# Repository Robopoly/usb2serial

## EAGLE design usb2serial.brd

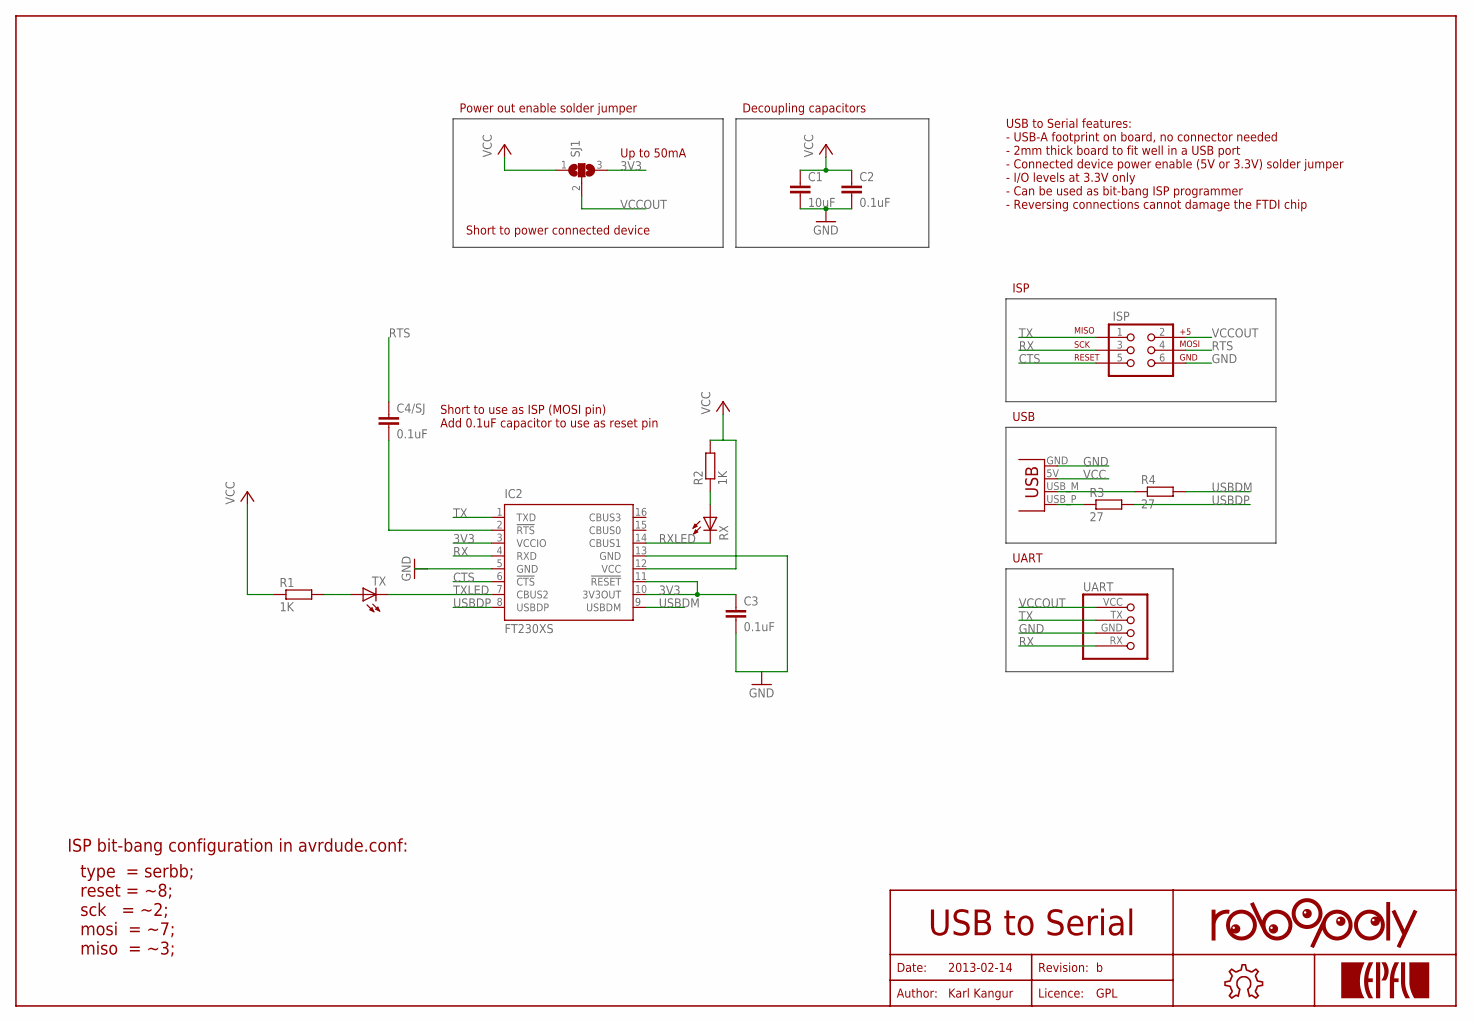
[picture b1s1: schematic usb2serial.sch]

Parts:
C1: 10uF; C0805
C2, C3, C4/SJ: 0.1uF; C0805
IC2: FT230XS; SSOP16
ISP: ISP-6PIN; 2X3
JP1: USBPCB; USB-A-PCB
R1, R2: 1K; R0805
R3, R4: 27; R0805
RX: LEDCHIPLED_0805; CHIPLED_0805
SJ1: SJ2W; SJ_2
TX: LEDCHIPLED_0805; CHIPLED_0805
U$1: UART-ROBOPOLY90; 929835-01-04-RK
U$2: ROBOPOLY-LOGOBOTTOM; ROBOPOLY-LOGO-BOTTOM
U$3: OPEN-HARDWARE-LOGOBOTTOM-SMALL; OPEN-HARDWARE-BOTTOM-SMALL

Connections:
3V3: C3.1, IC2.3 (VCCIO), IC2.10 (3V3OUT), IC2.11 (!RESET), SJ1.3
CTS: IC2.6 (!CTS), ISP.5
GND: C1.2, C2.2, C3.2, IC2.5 (GND), IC2.13 (GND), ISP.6, JP1.GND, U$1.GND (3)
unnamed: JP1.USB_M (D-), R4.1
unnamed: R1.2, TX.A
unnamed: C4/SJ.2, IC2.2 (!RTS)
unnamed: R2.1, RX.A
unnamed: JP1.USB_P (D+), R3.1
RTS: C4/SJ.1, ISP.4
RX: IC2.4 (RXD), ISP.3, U$1.RX (4)
RXLED: IC2.14 (CBUS1), RX.C
TX: IC2.1 (TXD), ISP.1, U$1.TX (2)
TXLED: IC2.7 (CBUS2), TX.C
USBDM: IC2.9 (USBDM), R4.2
USBDP: IC2.8 (USBDP), R3.2
VCC: C1.1, C2.1, IC2.12 (VCC), JP1.5V (VBUS), R1.1, R2.2, SJ1.1
VCCOUT: ISP.2, SJ1.2, U$1.VCC (1)

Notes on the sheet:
Power out enable solder jumper
ISP
USB
UART
Up to 50mA
Short to use as ISP (MOSI pin) Add 0.1uF capacitor to use as reset pin
Short to power connected device
USB to Serial features: - USB-A footprint on board, no connector needed - 2mm thick board to fit well in a USB port - Connected device power enable (5V or 3.3V) solder jumper - I/O levels at 3.3V only - Can be used as bit-bang ISP programmer - Reversing connections cannot damage the FTDI chip
Date:
Author:
Licence:
Revision:
2013-02-14
Karl Kangur
GPL
USB to Serial
Decoupling capacitors
ISP bit-bang configuration in avrdude.conf:
type = serbb; reset = ~8; sck = ~2; mosi = ~7; miso = ~3;

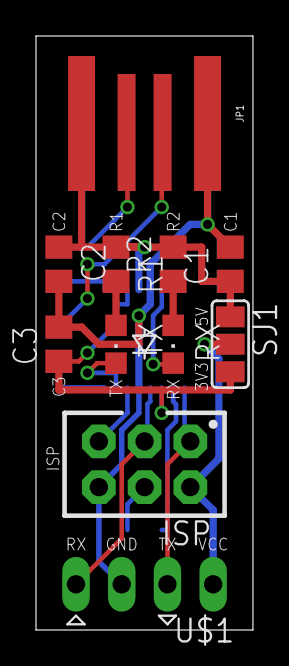
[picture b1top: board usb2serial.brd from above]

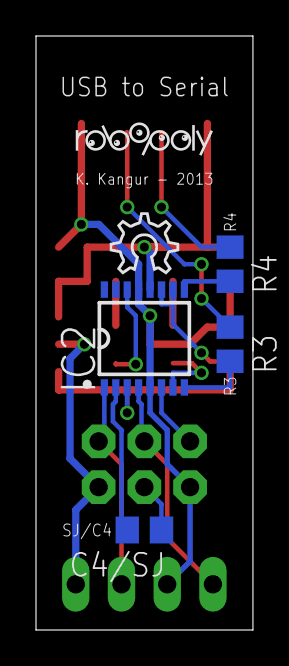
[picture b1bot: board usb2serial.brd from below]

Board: 2 copper layers, 12.1 x 33.0 mm, 17 parts (4 on the bottom side), 17 nets.

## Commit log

2013-02-25 Replaced the FT232R with FT230X chip

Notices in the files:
parts and their libraries:
SparkFun-Connectors: Licensing: CC v3.0 Share-Alike You are welcome to use this library for commercial purposes.
